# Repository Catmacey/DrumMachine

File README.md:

16 step sample based DrumMachine
================================

[Demo of features (Youtube)](https://www.youtube.com/watch?v=TWu0VHxkMRI)

This is a 16 track Sample based Drum Machine built on a 32bit PIC (PIC32mx150f128b).

The project hardware is relatively simple in that it limits itself to using the PIC's internal Flash for sample storage and the built in OC PWM for output. 

The Drum Machine has 16 tracks (instruments) of 16 steps and can save the song to one of 16 slots on a uSD card.

Features : Updated 24 / 8 / 2019

* 16 different instruments stored in Flash (Length dependant on sample quality/size).
* 16 step patterns with 16 patterns per song.
* 16 songs loaded and saved to FAT formatted uSD card.
* 8 sample polyphony, mixed in software.
* 10bit, 16khz instruments sampled from classic drum machines. (stored as 8bit log similar to uLaw)
* Samples can be "tuned" to playback faster/slower, louder quieter and can also have the in/out points set.
* "Jam Mode" to add some variety to your tracks by fading in/out each track as it plays.
* Swing
* Basic Reverb mode.
* Analog mono output filtered from an 10bit PWM signal.
* 16 buttons for beat input plus 4 more and 4-way joystick for interface.
* 20 leds driven by a Maxim 6957 LED driver to provide feedback.
* [Nokia 1202 B/W LCD](https://github.com/Catmacey/Nokia1202LCD-breakout) mounted on a breakout board displays user interface.
* Songs are stored as plain text in JSON format to allow some human readability.

[More information is available on my blog.](https://catmacey.wordpress.com/tag/drum-machine/)

Copyright (C) 2016 Matt Casey : catmacey.com
This program is free software: you can redistribute it and/or modify it under the terms of the GNU General Public License as published by the Free Software Foundation, either version 3 of the License, or (at your option) any later version.
	
This program is distributed in the hope that it will be useful, but WITHOUT ANY WARRANTY; without even the implied warranty of MERCHANTABILITY or FITNESS FOR A PARTICULAR PURPOSE.  See the GNU General Public License for more details.

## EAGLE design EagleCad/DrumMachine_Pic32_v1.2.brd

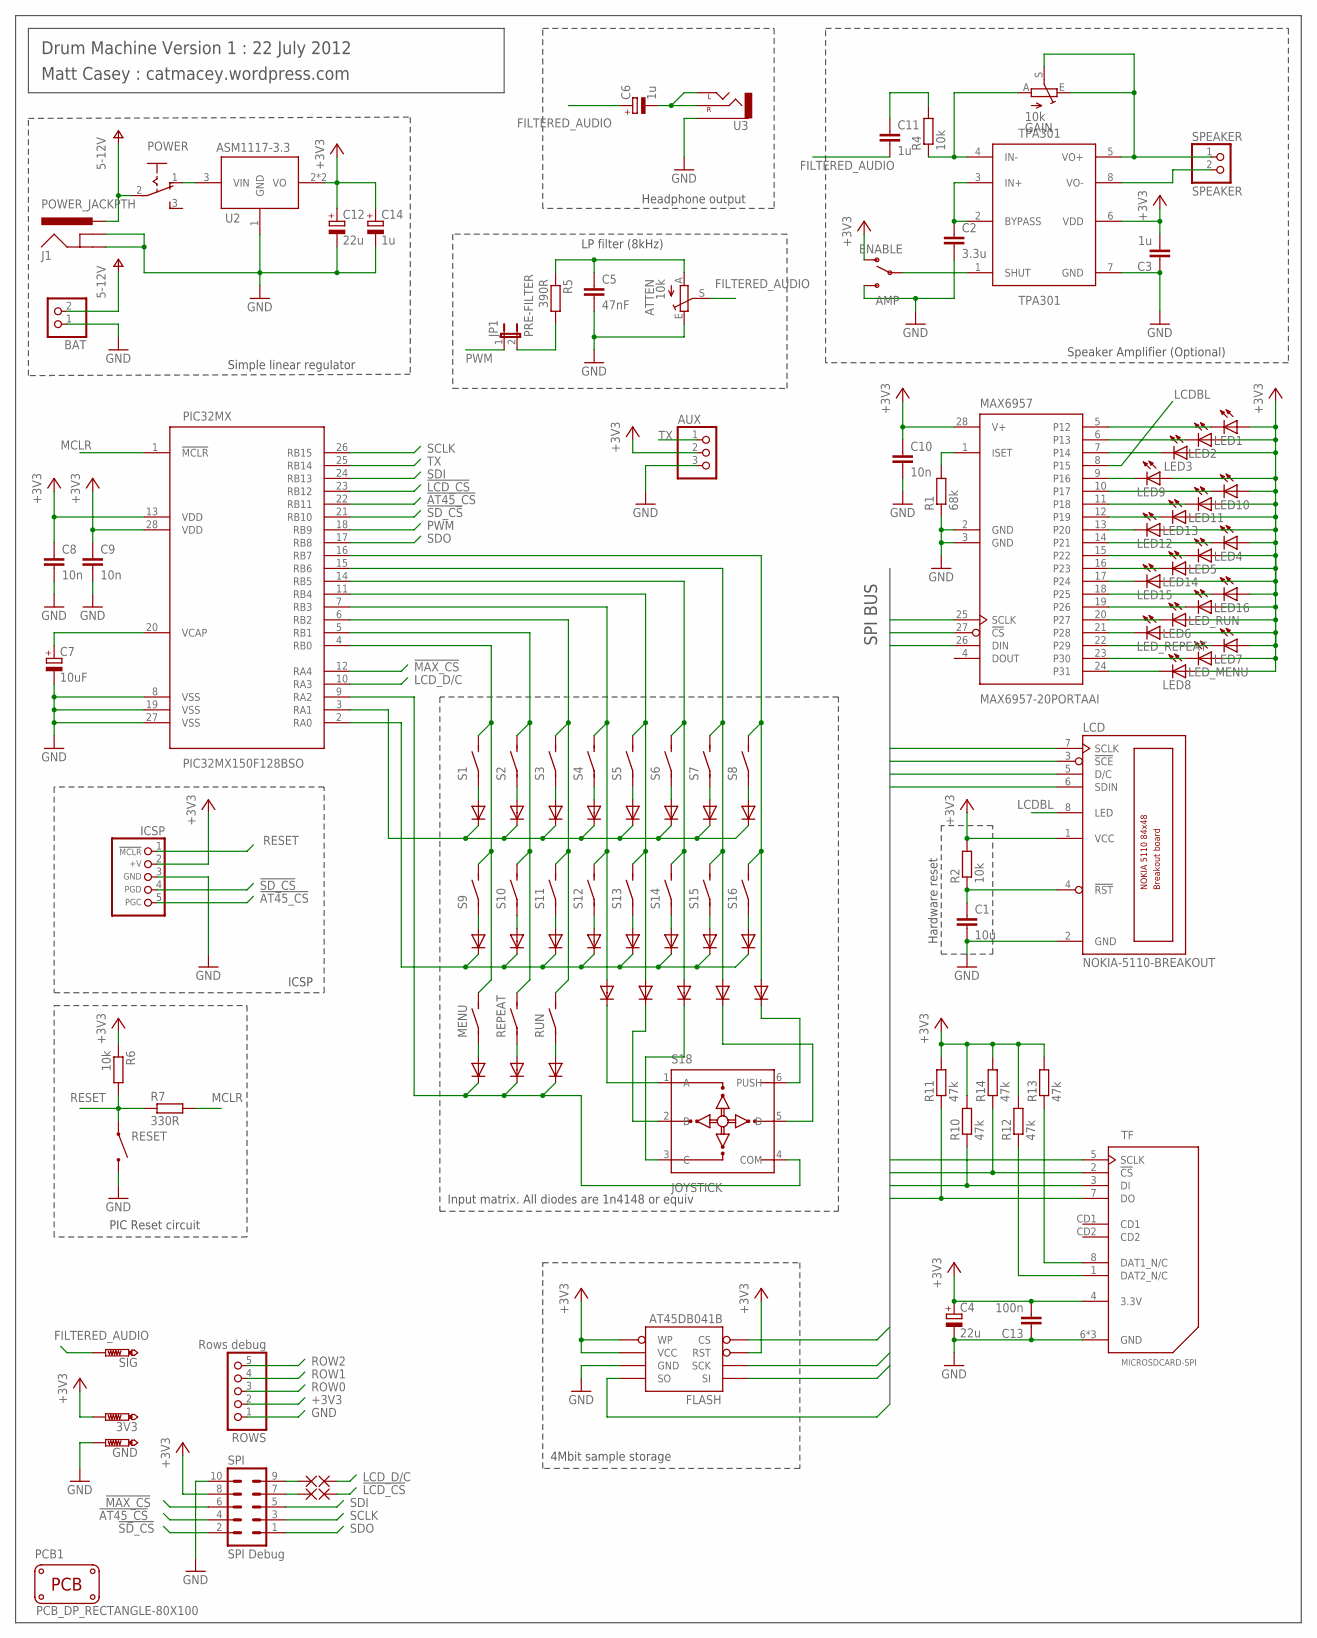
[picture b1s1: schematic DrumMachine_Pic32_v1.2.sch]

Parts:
3V3: PTR1PAD1-13; P1-13
AMP: ENABLE; SWITCH-SPST-SMD-A
ATTEN: 10k; CA6V
AUX: PINHD-1X3; 1X03
BAT: PINHD-1X2; 1X02
C1: 10u; C0805
C2: 3.3u; C0805
C3, C11: 1u; C0805
C4, C12: 22u; SMC_A
C5: 47nF; C0805
C6, C14: 1u; 153CLV-0405
C7: 10uF; SMC_A
C8, C9, C10: 10n; C0805
C13: 100n; C0805
D1, D2, D3, D4, D5, D6, D7, D8, D9, D10, D11, D12, D13, D14, D15, D16, D17, D18, D19, D20, D21, D22, D23, D25: DIODE-SOD-123; SOD-123
FLASH: AT45DB041B; SO08
GAIN: 10k; CA6V
GND: PTR1PAD1-13; P1-13
ICSP: CON_HEADER_PRG_PIC_ICSPB; HEADER_PRG_1X05_ICSP_B
J1: POWER_JACKPTH; POWER_JACK_PTH
JP1: PRE-FILTER; JP1
LCD: NOKIA-5110-BREAKOUT
LED1, LED2, LED3, LED4, LED5, LED6, LED7, LED8, LED9, LED10, LED11, LED12, LED13, LED14, LED15, LED16: LEDCHIPLED_0805; CHIPLED_0805
LED_MENU: LEDCHIPLED_0805; CHIPLED_0805
LED_REPEAT: LEDCHIPLED_0805; CHIPLED_0805
LED_RUN: LEDCHIPLED_0805; CHIPLED_0805
MAX6957: MAX6957-20PORTAAI; SSOP28
MENU: ITT-PTS645SMD
P1: DEBUG_LCD_CS; 1,2/0,5
P1A: LCD CS; 1,2/0,5
P2: DEBUG_LCD_D/c; 1,2/0,5
P2A: 1,6/0,81.2/0.5; 1,2/0,5
PCB1: PCB_DP_RECTANGLE-80X100; DP10080_V1
PIC32MX: PIC32MX150F128BSO; SO-28
POWER: DX_MINI_SPDT; DX_MINI_SPDT_VERTICAL
R1: 68k; R0805
R2, R4, R6: 10k; R0805
R5: 390R; R0805
R7: 330R; R0805
R10, R11, R12, R13, R14: 47k; R0805
REPEAT: ITT-PTS645SMD
RESET: TINY_TACTILESMD; TINY_TACTILE_SMD
ROWS: Rows debug; 1X05
RUN: ITT-PTS645SMD
S1, S2, S3, S4, S5, S6, S7, S8, S9, S10, S11, S12, S13, S14, S15, S16: ITT-PTS645SMD
S18: JOYSTICK; ALPS_SKQU_JOYSTICK
SIG: PTR1PAD1-13; P1-13
SPEAKER: SPEAKER; 1X02
SPI: SPI Debug; MA05-2
TF: MICROSDCARD-SPI; TCF001_MICROSD_SOCKET
TPA301: TPA301; SO-08
U2: ASM1117-3.3; SOT223
U3: AUDIO-JACKPTH; STEREO_JACK3.5MM_PTH

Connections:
!AT45_CS: FLASH.4 (CS), ICSP.5 (PGC), PIC32MX.22 (RB11), SPI.4
!LCDRST: C1.1, LCD.4 (!RST), R2.1
!LCD_CS: LCD.3 (!SCE), P1.1, P1A.1, PIC32MX.23 (RB12), SPI.7
!MAX_CS: MAX6957.27 (!CS), PIC32MX.12 (RA4), SPI.6
!SD_CS: ICSP.4 (PGD), PIC32MX.21 (RB10), R14.1, SPI.2, TF.2 (!CS)
+3V3: 3V3.TP, AMP.1 (O), AUX.2, C3.2, C4.+, C8.1, C9.1, C10.1, C12.+, C13.2, C14.+, FLASH.3 (RST), FLASH.5 (WP), FLASH.6 (VCC), ICSP.2 (+V), LCD.1 (VCC), LED1.A, LED2.A, LED3.A, LED4.A, LED5.A, LED6.A, LED7.A, LED8.A, LED9.A, LED10.A, LED11.A, LED12.A, LED13.A, LED14.A, LED15.A, LED16.A, LED_MENU.A, LED_REPEAT.A, LED_RUN.A, MAX6957.28 (V+), PIC32MX.13 (VDD), PIC32MX.28 (VDD), R2.2, R6.1, R10.2, R11.2, R12.2, R13.2, R14.2, ROWS.2, SPI.8, TF.4 (3.3V), TPA301.6 (VDD), U2.2 (VO), U2.4 (VO)
COL0: MENU.P$3 (2), MENU.P$4 (2), PIC32MX.4 (RB0), S1.P$3 (2), S1.P$4 (2), S9.P$3 (2), S9.P$4 (2)
COL1: PIC32MX.5 (RB1), REPEAT.P$3 (2), REPEAT.P$4 (2), S2.P$3 (2), S2.P$4 (2), S10.P$3 (2), S10.P$4 (2)
COL2: PIC32MX.6 (RB2), RUN.P$3 (2), RUN.P$4 (2), S3.P$3 (2), S3.P$4 (2), S11.P$3 (2), S11.P$4 (2)
COL3: D19.A, PIC32MX.7 (RB3), S4.P$3 (2), S4.P$4 (2), S12.P$3 (2), S12.P$4 (2)
COL4: D20.A, PIC32MX.11 (RB4), S5.P$3 (2), S5.P$4 (2), S13.P$3 (2), S13.P$4 (2)
COL5: D21.A, PIC32MX.14 (RB5), S6.P$3 (2), S6.P$4 (2), S14.P$3 (2), S14.P$4 (2)
COL6: D22.A, PIC32MX.15 (RB6), S7.P$3 (2), S7.P$4 (2), S15.P$3 (2), S15.P$4 (2)
COL7: D23.A, PIC32MX.16 (RB7), S8.P$3 (2), S8.P$4 (2), S16.P$3 (2), S16.P$4 (2)
FILTERED_AUDIO: ATTEN.S, C6.+, C11.2, SIG.TP
GND: AMP.3 (S), ATTEN.E, AUX.3, BAT.1, C1.2, C2.2, C3.1, C4.-, C5.2, C7.-, C8.2, C9.2, C10.2, C12.-, C13.1, C14.-, FLASH.7 (GND), GND.TP, ICSP.3 (GND), J1.GND, J1.GNDBREAK, LCD.2 (GND), MAX6957.2 (GND), MAX6957.3 (GND), PIC32MX.8 (VSS), PIC32MX.19 (VSS), PIC32MX.27 (VSS), R1.1, RESET.2 (B), ROWS.1, SPI.10, TF.6 (GND), TF.P$11 (GND), TF.P$12 (GND), TPA301.7 (GND), U2.1 (GND), U3.S (SLEEVE), U3.S@1 (SLEEVE)
LCDBL: LCD.8 (LED), MAX6957.8 (P15)
LCD_D/C: LCD.5 (D/C), P2.1, P2A.1, PIC32MX.10 (RA3), SPI.9
MCLR: PIC32MX.1 (!MCLR), R7.2
unnamed: D25.A, S1.P$1 (1), S1.P$2 (1)
unnamed: D1.A, S2.P$1 (1), S2.P$2 (1)
unnamed: D2.A, S3.P$1 (1), S3.P$2 (1)
unnamed: D3.A, S4.P$1 (1), S4.P$2 (1)
unnamed: D4.A, S5.P$1 (1), S5.P$2 (1)
unnamed: D5.A, S6.P$1 (1), S6.P$2 (1)
unnamed: D6.A, S7.P$1 (1), S7.P$2 (1)
unnamed: D7.A, S8.P$1 (1), S8.P$2 (1)
unnamed: LED1.C, MAX6957.5 (P12)
unnamed: LED2.C, MAX6957.6 (P13)
unnamed: LED3.C, MAX6957.7 (P14)
unnamed: LED12.C, MAX6957.13 (P20)
unnamed: LED11.C, MAX6957.11 (P18)
unnamed: LED10.C, MAX6957.10 (P17)
unnamed: LED9.C, MAX6957.9 (P16)
unnamed: LED4.C, MAX6957.14 (P21)
unnamed: LED13.C, MAX6957.12 (P19)
unnamed: LED14.C, MAX6957.16 (P23)
unnamed: LED15.C, MAX6957.17 (P24)
unnamed: D18.A, MENU.P$1 (1), MENU.P$2 (1)
unnamed: D17.A, REPEAT.P$1 (1), REPEAT.P$2 (1)
unnamed: D16.A, RUN.P$1 (1), RUN.P$2 (1)
unnamed: LED16.C, MAX6957.18 (P25)
unnamed: D19.C, S18.1 (A)
unnamed: D8.A, S9.P$1 (1), S9.P$2 (1)
unnamed: LED5.C, MAX6957.15 (P22)
unnamed: D9.A, S10.P$1 (1), S10.P$2 (1)
unnamed: D10.A, S11.P$1 (1), S11.P$2 (1)
unnamed: D11.A, S12.P$1 (1), S12.P$2 (1)
unnamed: D12.A, S13.P$1 (1), S13.P$2 (1)
unnamed: D13.A, S14.P$1 (1), S14.P$2 (1)
unnamed: D14.A, S15.P$1 (1), S15.P$2 (1)
unnamed: D15.A, S16.P$1 (1), S16.P$2 (1)
unnamed: LED6.C, MAX6957.20 (P27)
unnamed: D20.C, S18.2 (B)
unnamed: D22.C, S18.5 (D)
unnamed: D23.C, S18.6 (PUSH)
unnamed: D21.C, S18.3 (C)
unnamed: LED7.C, MAX6957.22 (P29)
unnamed: LED8.C, MAX6957.24 (P31)
unnamed: LED_RUN.C, MAX6957.19 (P26)
unnamed: LED_REPEAT.C, MAX6957.21 (P28)
unnamed: LED_MENU.C, MAX6957.23 (P30)
unnamed: AMP.2, TPA301.1 (SHUT)
unnamed: MAX6957.1 (ISET), R1.2
unnamed: POWER.1 (O), U2.3 (VIN)
unnamed: C2.1, TPA301.2 (BYPASS), TPA301.3 (IN+)
unnamed: GAIN.E, GAIN.S, SPEAKER.1, TPA301.5 (VO+)
unnamed: C7.+, PIC32MX.20 (VCAP)
unnamed: GAIN.A, R4.1, TPA301.4 (IN-)
unnamed: C11.1, R4.2
unnamed: C6.-, U3.L (LEFT), U3.L@1 (LEFT), U3.R (RIGHT)
unnamed: ATTEN.A, C5.1, R5.1
unnamed: R13.1, TF.8 (DAT1_N/C)
unnamed: R12.1, TF.1 (DAT2_N/C)
unnamed: SPEAKER.2, TPA301.8 (VO-)
PWM: JP1.1, PIC32MX.18 (RB9)
PWM2: JP1.2, R5.2
RESET: ICSP.1 (/MCLR), R6.2, R7.1, RESET.1 (A)
ROW0: D1.C, D2.C, D3.C, D4.C, D5.C, D6.C, D7.C, D25.C, PIC32MX.3 (RA1), ROWS.3
ROW1: D8.C, D9.C, D10.C, D11.C, D12.C, D13.C, D14.C, D15.C, PIC32MX.2 (RA0), ROWS.4
ROW2: D16.C, D17.C, D18.C, PIC32MX.9 (RA2), ROWS.5, S18.4 (COM)
SCLK: FLASH.2 (SCK), LCD.7 (SCLK), MAX6957.25 (SCLK), PIC32MX.26 (RB15), SPI.3, TF.5 (SCLK)
SDI: FLASH.8 (SO), PIC32MX.24 (RB13), R11.1, SPI.5, TF.7 (DO)
SDO: FLASH.1 (SI), LCD.6 (SDIN), MAX6957.26 (DIN), PIC32MX.17 (RB8), R10.1, SPI.1, TF.3 (DI)
TX: AUX.1, PIC32MX.25 (RB14)
V+: BAT.2, J1.PWR, POWER.2

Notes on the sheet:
PIC Reset circuit
ICSP
Speaker Amplifier (Optional)
Headphone output
LP filter (8kHz)
Input matrix. All diodes are 1n4148 or equiv
Hardware reset
Simple linear regulator
Drum Machine Version 1 : 22 July 2012
Matt Casey : catmacey.wordpress.com
SPI BUS
4Mbit sample storage

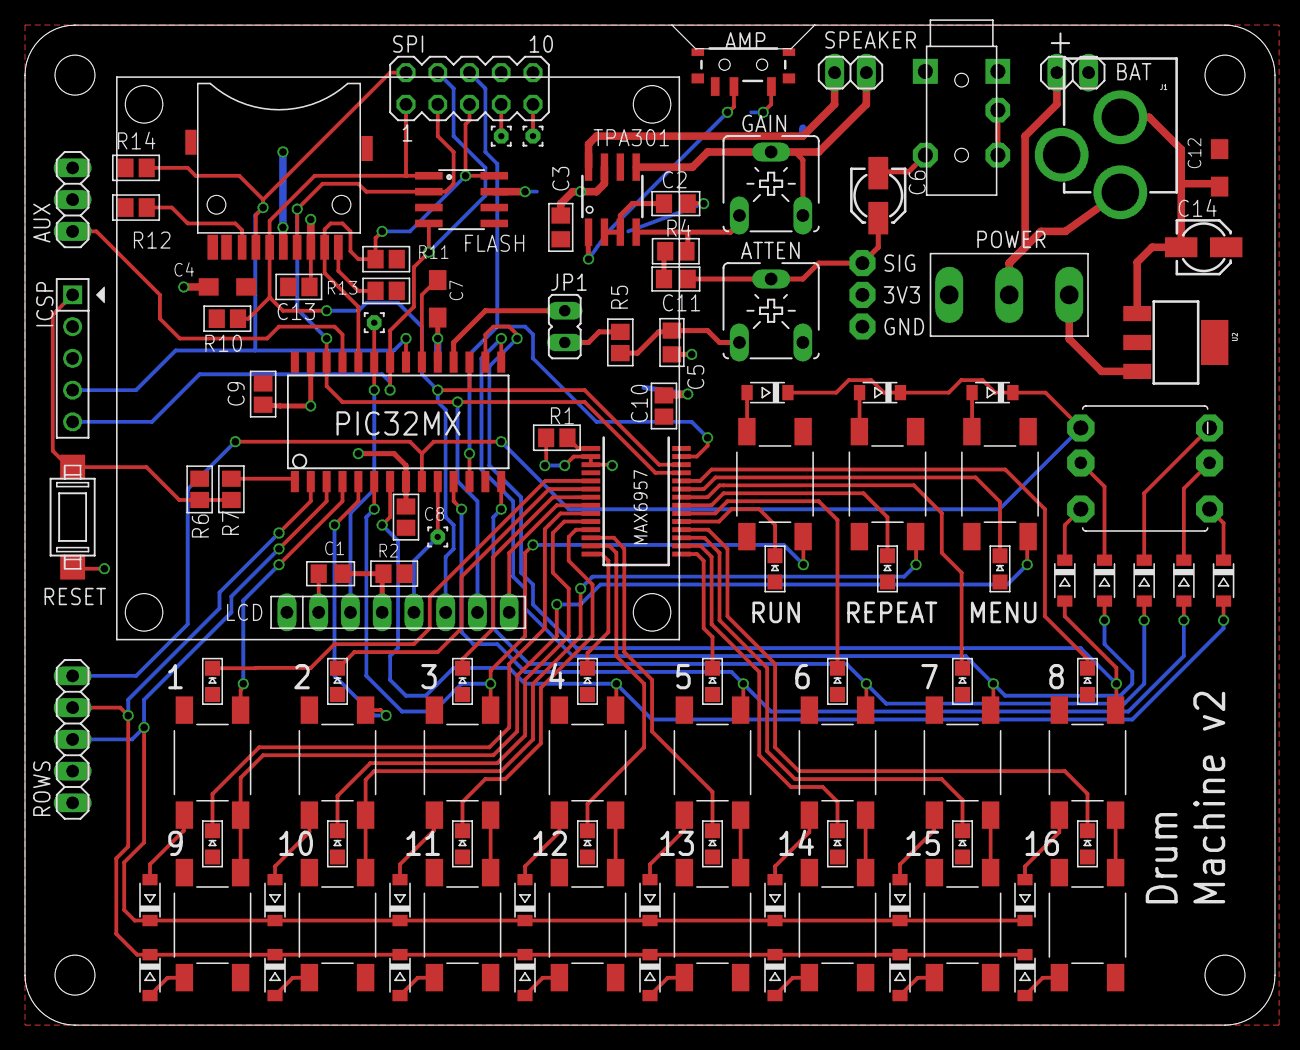
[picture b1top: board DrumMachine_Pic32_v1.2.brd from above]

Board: 2 copper layers, 100.0 x 80.0 mm, 117 parts (0 on the bottom side), 86 nets.

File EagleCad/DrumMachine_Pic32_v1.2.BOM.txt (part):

Partlist exported from DrumMachine_Pic32_v1.2.sch at 19/03/2016 18:22:23

Part       Value                    Device                   Package                Description                                                   MF MPN OC_FARNELL OC_NEWARK TP_SIGNAL_NAME
3V3        PTR1PAD1-13              PTR1PAD1-13              P1-13                  TEST PIN                                                                                                
AMP        ENABLE                   SWITCH-SPST-SMD-A        SWITCH-SPST-SMD-A      SPST Switch                                                                                             
ATTEN      10k                      TRIM_EU-CA6V             CA6V                   POTENTIOMETER                                                                                           
AUX                                 PINHD-1X3                1X03                   PIN HEADER                                                                                              
BAT                                 PINHD-1X2                1X02                   PIN HEADER                                                                                              
C1         10u                      C-EUC0805                C0805                  CAPACITOR, European symbol                                                                              
C2         3.3u                     C-EUC0805                C0805                  CAPACITOR, European symbol                                                                              
C3         1u                       C-EUC0805                C0805                  CAPACITOR, European symbol                                                                              
C4         22u                      CPOL-EUSMCA              SMC_A                  POLARIZED CAPACITOR, European symbol                                                                    
C5         47nF                     C-EUC0805                C0805                  CAPACITOR, European symbol                                                                              
C6         1u                       CPOL-EU153CLV-0405       153CLV-0405            POLARIZED CAPACITOR, European symbol                                                                    
C7         10uF                     CPOL-EUSMCA              SMC_A                  POLARIZED CAPACITOR, European symbol                                                                    
C8         10n                      C-EUC0805                C0805                  CAPACITOR, European symbol                                                                              
C9         10n                      C-EUC0805                C0805                  CAPACITOR, European symbol                                                                              
C10        10n                      C-EUC0805                C0805                  CAPACITOR, European symbol                                                                              
C11        1u                       C-EUC0805                C0805                  CAPACITOR, European symbol                                                                              
C12        22u                      CPOL-EUSMCA              SMC_A                  POLARIZED CAPACITOR, European symbol                                                                    
C13        100n                     C-EUC0805                C0805                  CAPACITOR, European symbol                                                                              
C14        1u                       CPOL-EU153CLV-0405       153CLV-0405            POLARIZED CAPACITOR, European symbol                                                                    
D1                                  DIODE-SOD-123            SOD-123                Various Diode Packages                                                                                  
D2                                  DIODE-SOD-123            SOD-123                Various Diode Packages                                                                                  
D3                                  DIODE-SOD-123            SOD-123                Various Diode Packages                                                                                  
D4                                  DIODE-SOD-123            SOD-123                Various Diode Packages                                                                                  
D5                                  DIODE-SOD-123            SOD-123                Various Diode Packages                                                                                  
D6                                  DIODE-SOD-123            SOD-123                Various Diode Packages                                                                                  
D7                                  DIODE-SOD-123            SOD-123                Various Diode Packages                                                                                  
D8                                  DIODE-SOD-123            SOD-123                Various Diode Packages                                                                                  
D9                                  DIODE-SOD-123            SOD-123                Various Diode Packages                                                                                  
D10                                 DIODE-SOD-123            SOD-123                Various Diode Packages                                                                                  
D11                                 DIODE-SOD-123            SOD-123                Various Diode Packages                                                                                  
D12                                 DIODE-SOD-123            SOD-123                Various Diode Packages                                                                                  
D13                                 DIODE-SOD-123            SOD-123                Various Diode Packages                                                                                  
D14                                 DIODE-SOD-123            SOD-123                Various Diode Packages                                                                                  
D15                                 DIODE-SOD-123            SOD-123                Various Diode Packages                                                                                  
D16                                 DIODE-SOD-123            SOD-123                Various Diode Packages                                                                                  
D17                                 DIODE-SOD-123            SOD-123                Various Diode Packages                                                                                  
D18                                 DIODE-SOD-123            SOD-123                Various Diode Packages                                                                                  
D19                                 DIODE-SOD-123            SOD-123                Various Diode Packages                                                                                  
D20                                 DIODE-SOD-123            SOD-123                Various Diode Packages                                                                                  
D21                                 DIODE-SOD-123            SOD-123                Various Diode Packages                                                                                  
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
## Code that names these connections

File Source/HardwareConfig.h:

#ifndef _Config_H
#define _Config_H

/******* G E N E R I C   D E F I N I T I O N S ************************************************/

#define BYTETOBINARYPATTERN "%d%d%d%d%d%d%d%d"
#define BYTETOBINARY(byte)  \
  (byte & 0x80 ? 1 : 0), \
  (byte & 0x40 ? 1 : 0), \
  (byte & 0x20 ? 1 : 0), \
  (byte & 0x10 ? 1 : 0), \
  (byte & 0x08 ? 1 : 0), \
  (byte & 0x04 ? 1 : 0), \
  (byte & 0x02 ? 1 : 0), \
  (byte & 0x01 ? 1 : 0) 


#define	HIGH	1
#define	LOW	0
#define	OUTPUT	0
#define	INPUT 	1
//#define	SET	1
//#define	CLEAR	0

//#define GetSystemClock()  (40000000ul)
#define GetSystemClock()  (48000000ul)
//#define GetSystemClock()  (60000000ul)
//#define GetSystemClock()  (64000000ul)
#define GetPeripheralClock()    (GetSystemClock() / (1 << OSCCONbits.PBDIV))
#define TICKS_uS (GetSystemClock() / 1000000)/2   //sys clocks per micro second for core timer
#define TICKS_mS (GetSystemClock() / 1000)/2   //sys clocks per milli second for core timer


//Matrix Columns RB0 - 7
#define Col0 	_RB0
#define Col1 	_RB1
#define Col2 	_RB2
#define Col3 	_RB3
#define Col4 	_RB4
#define Col5 	_RB5
#define Col6 	_RB6
#define Col7 	_RB7

//Matrix Rows RA0 - 1
#define Row0 			_LATA1
#define Row1 			_LATA0
#define Row2 			_LATA2
#define Row0Tris 	_TRISA1
#define Row1Tris 	_TRISA0
#define Row2Tris 	_TRISA2

//PMW out
#define PWM _LATB9

//AT45 RAM CS
#define AT45_CS _LATB11

//Serial debug output
#define TX _LATB14
#define PPS_TX  PPS_RP14

//Spare GPIO (Used to be LCD D/C)
#define DAC_CS _LATA3

//SD Card
#define SD_CS _LATB10
#define SD_CS_ENABLE mPORTBClearBits(BIT_10);
#define SD_CS_CLEAR mPORTBSetBits(BIT_10);

#define SPICHANNEL 2

//NOKIA LCD PORT PIN DEFINTION
///****************************************************
// Hardware SPI
// Manual CS between each byte, but could be modified to do bulk transfers.
///****************************************************
#define LCD_CS 		_LATB12

#define LCD_CS_ENABLE() mPORTBClearBits(BIT_12)
#define LCD_CS_CLEAR() mPORTBSetBits(BIT_12)

#define SPI_CLK_HIGH() mPORTBSetBits(BIT_15)
#define SPI_CLK_LOW() mPORTBClearBits(BIT_15)

#define SPI_MOSI_HIGH() mPORTBSetBits(BIT_8)
#define SPI_MOSI_LOW() mPORTBClearBits(BIT_8)


//#define LCD_RST 	_LATB12 //Can be performed in hardware with R/C. saves pin

//#define LCD_BL 		_LATB9 //LED backlight PWM'd

//MAX6957
///****************************************************
// Hardware SPI
// Manual CS between each byte, but could be modified to do bulk transfers.
///****************************************************
#define MAX6957_CS 		_LATA4

#define LCDTYPE_NOKIA_1202


#endif

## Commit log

2016-03-19 :octocat: Added .gitattributes & .gitignore files
2016-03-19 Initial commit of current state of existing project
2016-03-19 Fixed formatting
2019-08-24 Major tidy up and some new features
2019-08-24 Added firmware HEX
    Added a compiled HEX for those that don't want the bother of setting up a project :o)
2019-08-24 Updated readme to include new features
2019-09-13 Update firmware.hex
    Replaced firmware with one that was exported from a running PIC. The previous one only seemed to work when programmed using MPLAB X not when using 3rd party tools.

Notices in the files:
parts and their libraries:
SparkFun: Licensing: CC v3.0 Share-Alike You are welcome to use this library for commercial purposes.
